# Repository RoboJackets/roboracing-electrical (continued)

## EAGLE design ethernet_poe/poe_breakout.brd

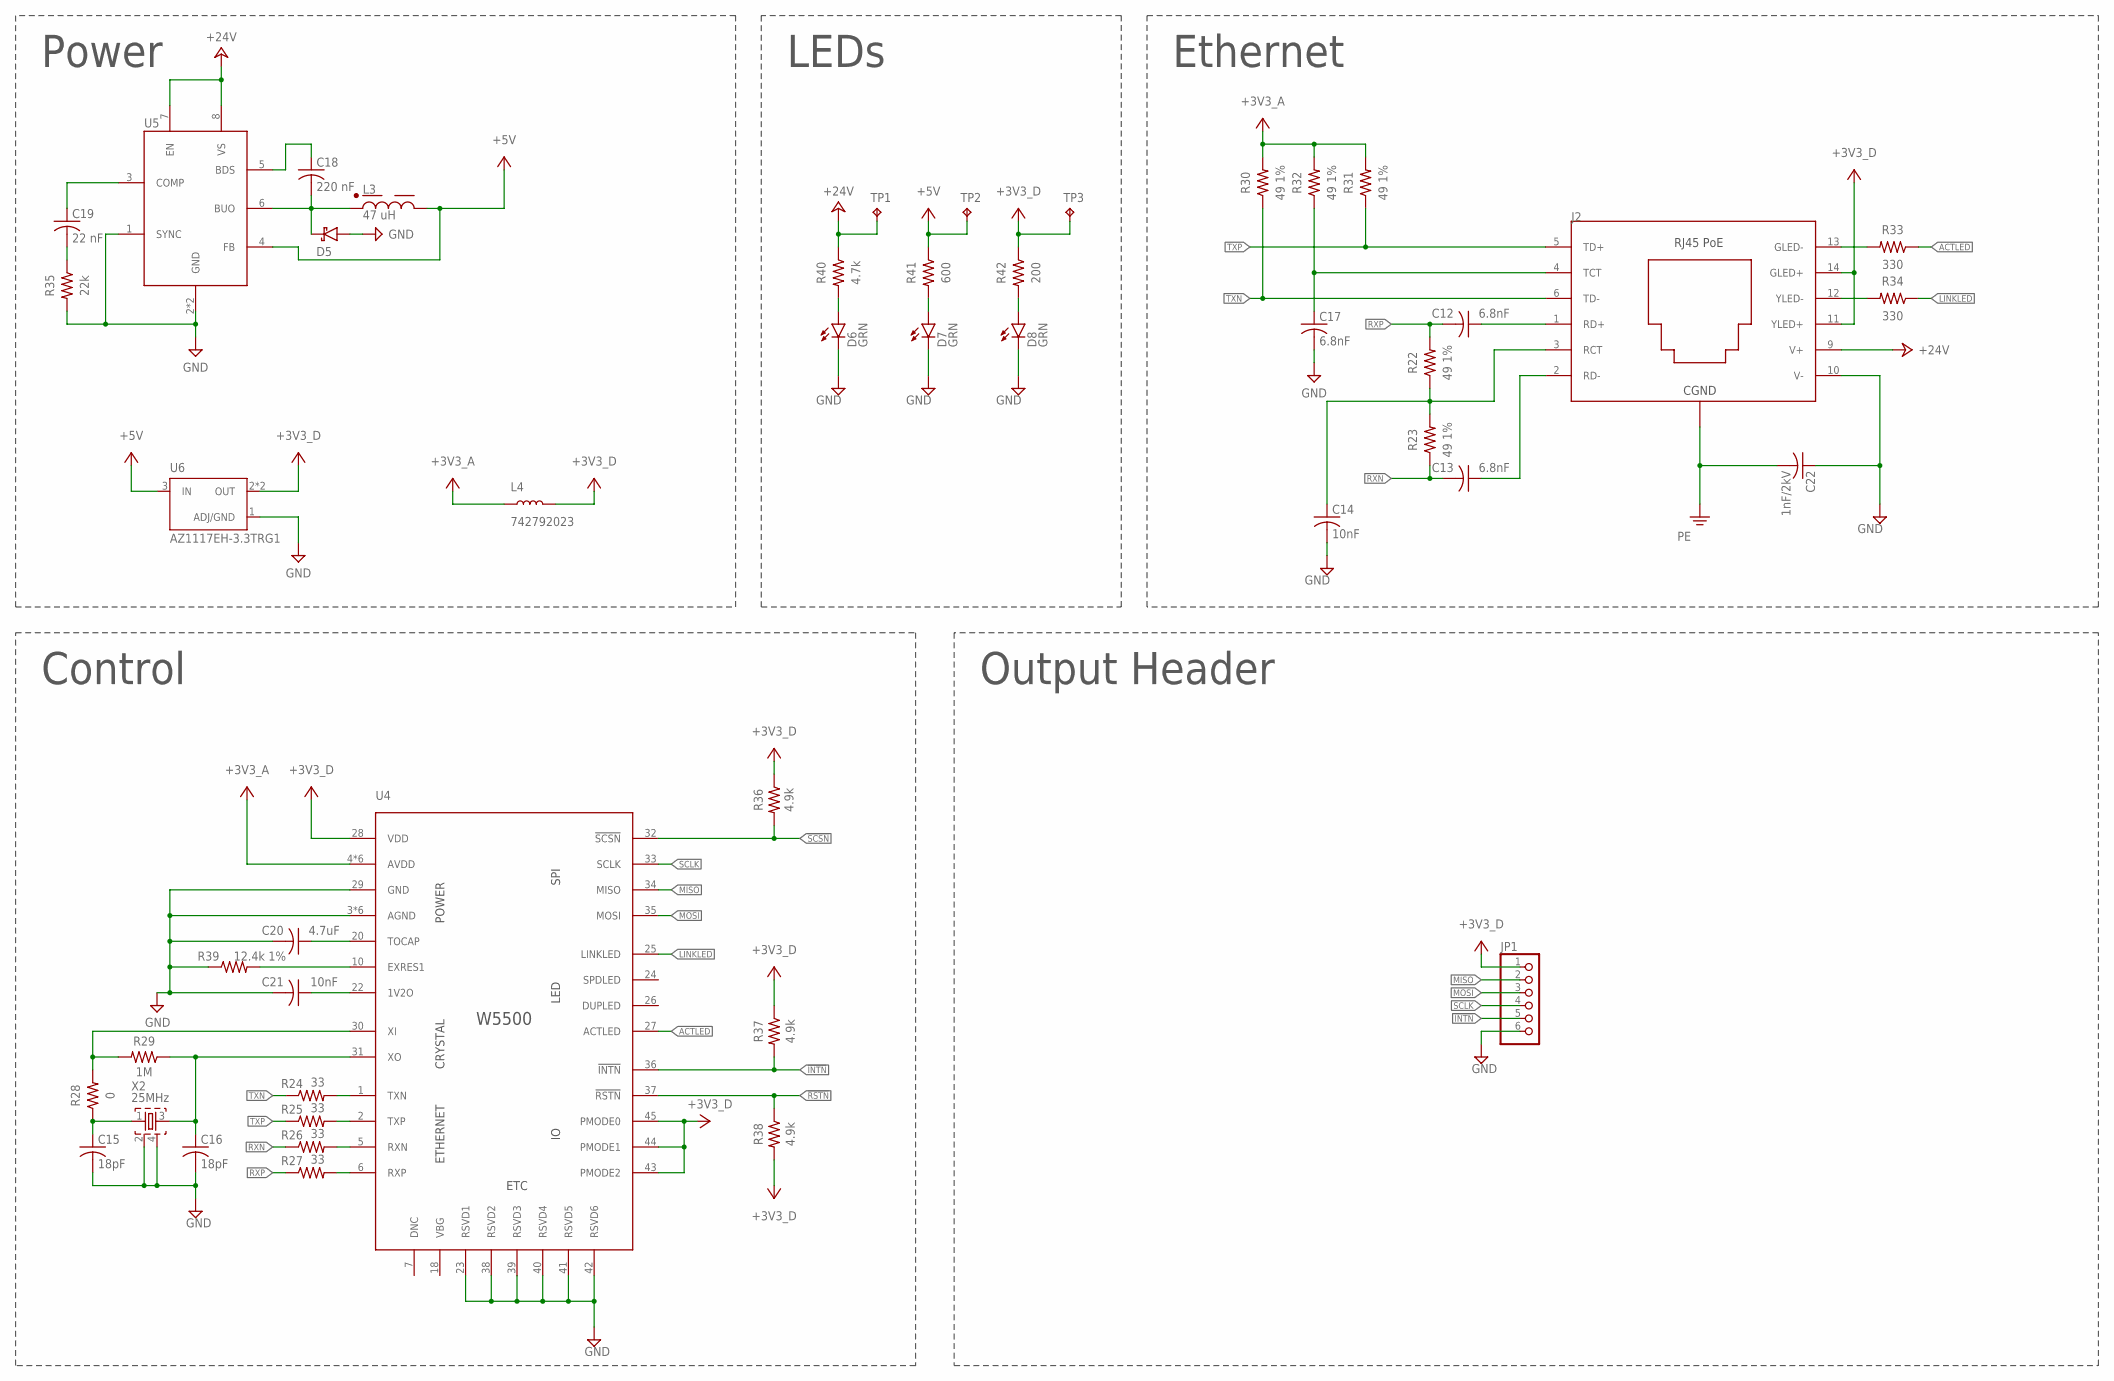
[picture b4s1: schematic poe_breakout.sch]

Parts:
C12, C13, C17: 6.8nF; C0603
C14, C21: 10nF; C0603
C15, C16: 18pF; C0603
C18: 220 nF; C0603
C19: 22 nF; C0603
C20: 4.7uF; C0603
C22: 1nF/2kV; C1206
D5: SCHOTTKYSOD-323; SOD-323
D6, D7, D8: GRN; CHIP-LED0603
J2: ARJP11A; ARJP11A-MBSB-A-B-EMU2
JP1: PINHD-1X6; 1X06
L3: 47 uH; 744771147
L4: 742792023; 0805
R22, R23, R30, R31, R32: 49 1%; R0603
R24, R25, R26, R27: 33; R0603
R28: 0; R0603
R29: 1M; R0603
R33, R34: 330; R0603
R35: 22k; R0603
R36, R37, R38: 4.9k; R0603
R39: 12.4k 1%; R0603
R40: 4.7k; R0603
R41: 600; R0603
R42: 200; R0603
TP1, TP2, TP3: TPB1,27; B1,27
U4: W5500; 48-LQFP
U5: IFX91041; SOIC-8-EXPOSED_PAD
U6: AZ1117EH-3.3TRG1; SOT230P700X180-4N
X2: 25MHz; OSCILLATOR-SMD-2.5X2

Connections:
3V3_LED1: D8.A, R42.2
5V_LED1: D7.A, R41.2
24V_LED1: D6.A, R40.2
!INTN: JP1.5, R37.2, U4.36 (!INTN)
!RSTN: R38.1, U4.37 (!RSTN)
!SCSN: R36.2, U4.32 (!SCSN)
+3V3_A: L4.1, R30.2, R31.2, R32.2, U4.4 (AVDD), U4.8 (AVDD), U4.11 (AVDD), U4.15 (AVDD), U4.17 (AVDD), U4.21 (AVDD)
+3V3_D: J2.11 (YLED+), J2.14 (GLED+), JP1.1, L4.2, R36.1, R37.1, R38.2, R42.1, TP3.TP, U4.28 (VDD), U4.43 (PMODE2), U4.44 (PMODE1), U4.45 (PMODE0), U6.2 (OUT), U6.4 (OUT)
+5V: L3.1, R41.1, TP2.TP, U5.4 (FB), U6.3 (IN)
+24V: J2.9 (V+), R40.1, TP1.TP, U5.7 (EN), U5.8 (VS)
ACTLED: R33.1, U4.27 (ACTLED)
GND: C14.2, C15.2, C16.2, C17.2, C20.2, C21.2, C22.1, D5.A, D6.C, D7.C, D8.C, J2.10 (V-), JP1.6, R35.2, R39.1, U4.3 (AGND), U4.9 (AGND), U4.14 (AGND), U4.16 (AGND), U4.19 (AGND), U4.23 (RSVD1), U4.29 (GND), U4.38 (RSVD2), U4.39 (RSVD3), U4.40 (RSVD4), U4.41 (RSVD5), U4.42 (RSVD6), U4.48 (AGND), U5.1 (SYNC), U5.2 (GND), U5.P$9 (GND), U6.1 (ADJ/GND), X2.2 (SHD1), X2.4 (SHD2)
LINKLED: R34.1, U4.25 (LINKLED)
MISO: JP1.2, U4.34 (MISO)
MOSI: JP1.3, U4.35 (MOSI)
unnamed: R24.2, U4.1 (TXN)
unnamed: R25.2, U4.2 (TXP)
unnamed: R26.2, U4.5 (RXN)
unnamed: R27.2, U4.6 (RXP)
unnamed: C15.1, R28.1, X2.1 (IN)
unnamed: R28.2, R29.2, U4.30 (XI)
unnamed: C16.1, R29.1, U4.31 (XO), X2.3 (OUT)
unnamed: J2.12 (YLED-), R34.2
unnamed: J2.13 (GLED-), R33.2
unnamed: C18.2, D5.C, L3.P$2, U5.6 (BUO)
unnamed: C18.1, U5.5 (BDS)
unnamed: C19.2, R35.1
unnamed: C19.1, U5.3 (COMP)
unnamed: C21.1, U4.22 (1V2O)
unnamed: C20.1, U4.20 (TOCAP)
unnamed: R39.2, U4.10 (EXRES1)
PE: C22.2, J2.15 (CGND), J2.16 (CGND)
RCT1: C14.1, J2.3 (RCT), R22.1, R23.2
RD+1: C12.1, J2.1 (RD+)
RD-1: C13.1, J2.2 (RD-)
RXN: C13.2, R23.1, R26.1
RXP: C12.2, R22.2, R27.1
SCLK: JP1.4, U4.33 (SCLK)
TCT1: C17.1, J2.4 (TCT), R32.1
TXN: J2.6 (TD-), R24.1, R30.1
TXP: J2.5 (TD+), R25.1, R31.1

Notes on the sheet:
Power
Control
LEDs
Ethernet
Output Header

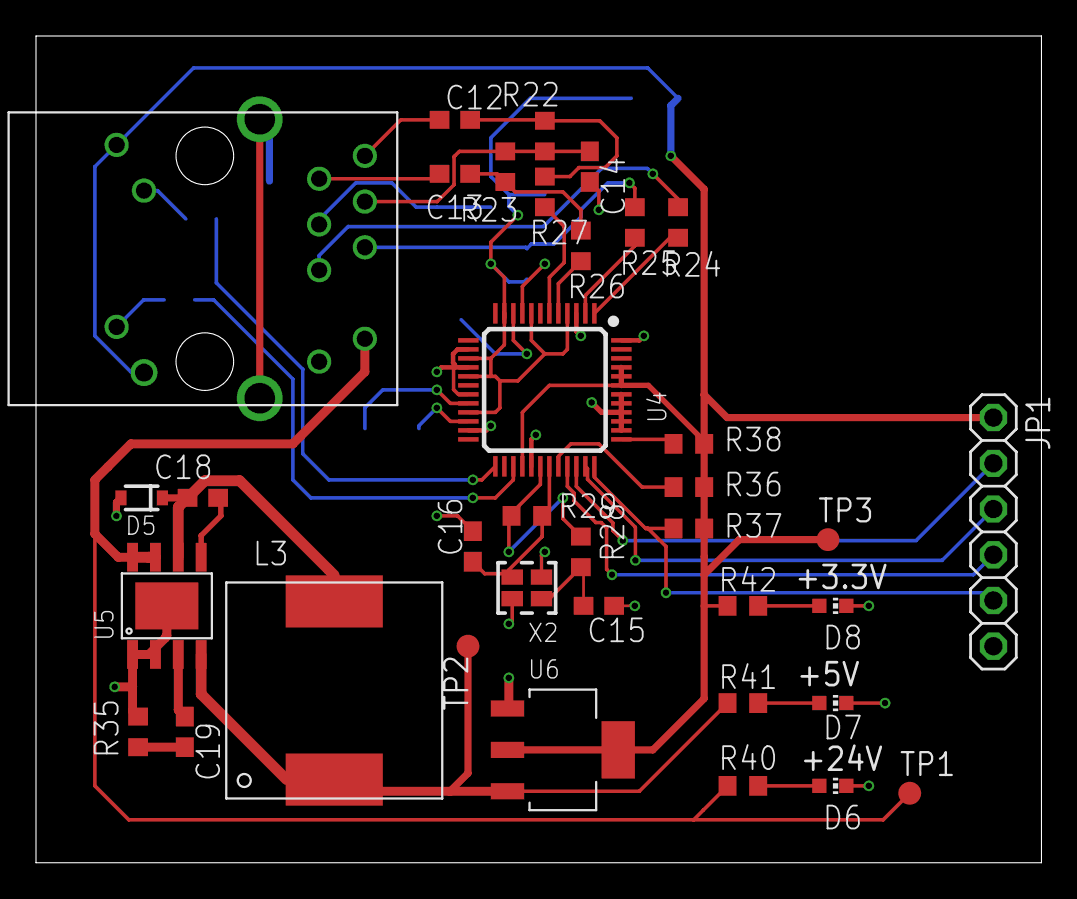
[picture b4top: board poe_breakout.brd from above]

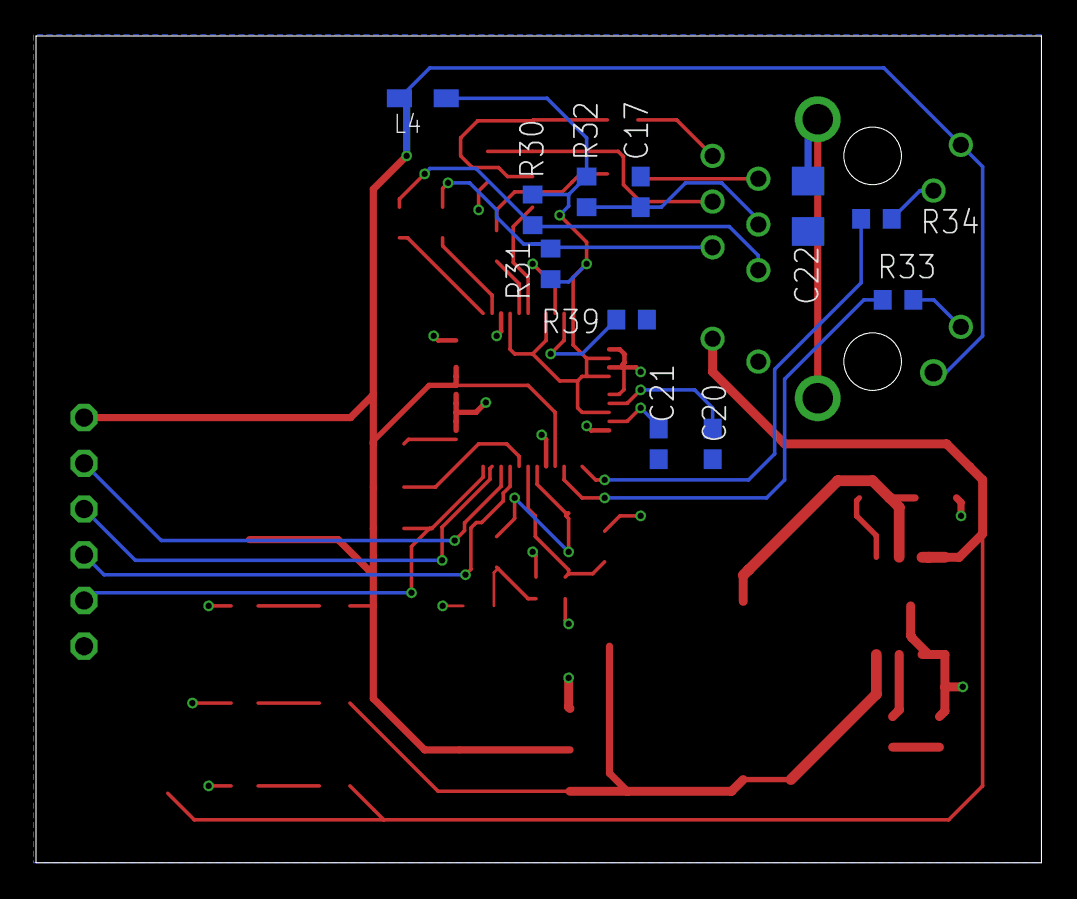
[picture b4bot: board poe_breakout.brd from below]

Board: 2 copper layers, 55.9 x 45.9 mm, 47 parts (11 on the bottom side), 41 nets.

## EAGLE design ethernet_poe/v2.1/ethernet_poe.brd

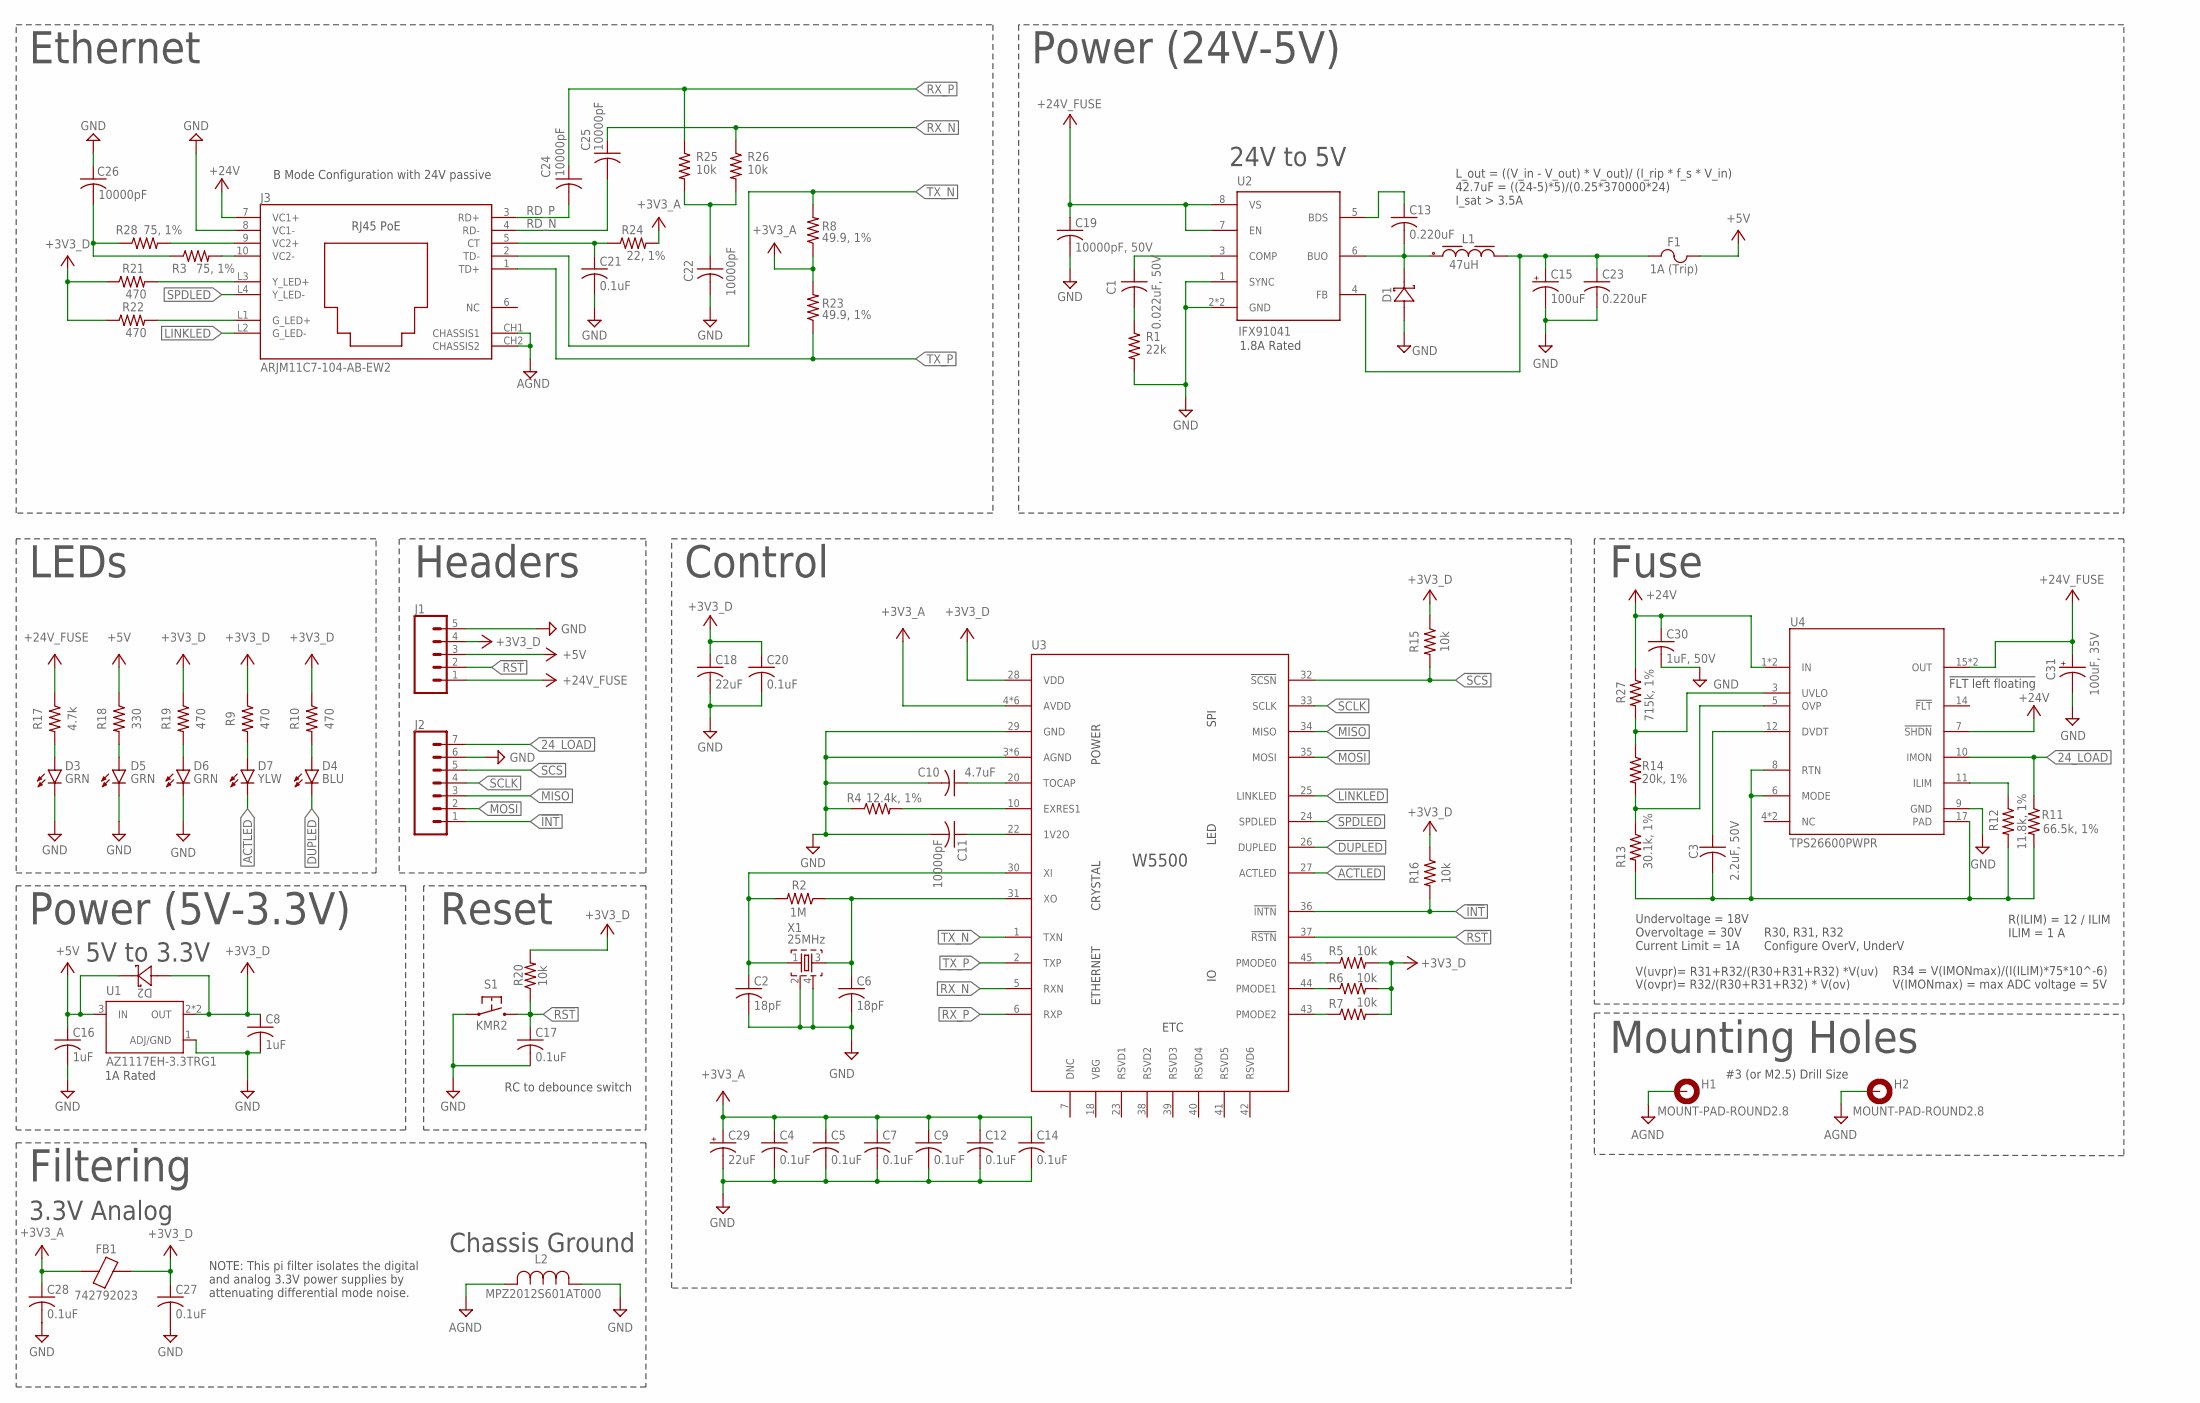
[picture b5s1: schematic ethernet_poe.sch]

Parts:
C1: 0.022uF, 50V; C0603
C2, C6: 18pF; C0603
C3: 2.2uF, 50V; C0603
C4, C5, C7, C9, C12, C14, C17, C20, C21: 0.1uF; C0402
C8, C16: 1uF; C0603
C10: 4.7uF; C0603
C11, C24, C25: 10000pF; C0402
C13, C23: 0.220uF; C0603
C15: 100uF; E2-5
C18: 22uF; C0603
C19: 10000pF, 50V; C0603
C22, C26: 10000pF; C0603
C27, C28: 0.1uF; C0603
C29: 22uF; PANASONIC_C
C30: 1uF, 50V; C0603
C31: 100uF, 35V; E2,5-7
D1, D2: NTS260ESFT3G; SOD123FL_DIO
D3, D5, D6: GRN; CHIP-LED0603
D4: BLU; CHIP-LED0603
D7: YLW; CHIP-LED0603
F1: 1A (Trip); 0ZCG_BEL
FB1: 742792023; 0805
H1, H2: MOUNT-PAD-ROUND2.8; 2,8-PAD
J1: CONN_05; 1X05
J2: CONN_07; 1X07
J3: ARJM11C7-104-AB-EW2; CONN_EW_ABR
L1: 47uH; WE-PD_1210
L2: MPZ2012S601AT000; IND_2012_TDK
R1: 22k; R0603
R2: 1M; R0402
R3, R28: 75, 1%; R0603
R4: 12.4k, 1%; R0603
R5, R6, R7, R15, R16, R20, R25, R26: 10k; R0603
R8, R23: 49.9, 1%; R0402
R9, R10, R19, R21, R22: 470; R0603
R11: 66.5k, 1%; R0603
R12: 11.8k, 1%; R0603
R13: 30.1k, 1%; R0603
R14: 20k, 1%; R0603
R17: 4.7k; R0603
R18: 330; R0603
R24: 22, 1%; R0603
R27: 715k, 1%; R0603
S1: KMR2
U1: AZ1117EH-3.3TRG1; SOT230P700X180-4N
U2: IFX91041; SOIC-8-EXPOSED_PAD
U3: W5500; 48-LQFP
U4: TPS26600PWPR; PWP0016H_N
X1: 25MHz; OSCILLATOR-SMD-2.5X2

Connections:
3V3_LED: D6.A, R19.2
3V3_LED1: D7.A, R9.2
3V3_LED2: D4.A, R10.2
5V_LED: D5.A, R18.2
5V_RAW: C13.2, D1.1, L1.1, U2.6 (BUO)
24V_LED: D3.A, R17.2
24_LOAD: J2.7, R11.1, U4.10 (IMON)
!INT: J2.1, R16.2, U3.36 (!INTN)
!RST: C17.1, J1.2, R20.1, S1.2.1 (2), S1.2.2 (2), U3.37 (!RSTN)
!SCS: J2.5, R15.2, U3.32 (!SCSN)
+3V3_A: C4.1, C5.1, C7.1, C9.1, C12.1, C14.1, C28.1, C29.+, FB1.1, R8.1, R23.2, R24.2, U3.4 (AVDD), U3.8 (AVDD), U3.11 (AVDD), U3.15 (AVDD), U3.17 (AVDD), U3.21 (AVDD)
+3V3_D: C8.1, C18.1, C20.1, C27.1, D2.2, FB1.2, J1.4, R5.2, R6.2, R7.2, R9.1, R10.1, R15.1, R16.1, R19.1, R20.2, R21.1, R22.1, U1.2 (OUT), U1.4 (OUT), U3.28 (VDD)
+5V: C16.1, D2.1, F1.2, J1.3, R18.1, U1.3 (IN)
+5V_PREFUSE: C15.+, C23.1, F1.1, L1.2, U2.4 (FB)
+24V: C30.1, J3.7 (VC1+), R27.1, U4.1 (IN), U4.2 (IN), U4.7 (!SHDN)
+24V_FUSE: C19.1, C31.+, J1.1, R17.1, U2.7 (EN), U2.8 (VS), U4.15 (OUT), U4.16 (OUT)
ACTLED: D7.C, U3.27 (ACTLED)
AGND: H1.B2,8, H2.B2,8, J3.CH1 (CHASSIS1), J3.CH2 (CHASSIS2), L2.2
CT: C21.1, J3.5 (CT), R24.1
DUPLED: D4.C, U3.26 (DUPLED)
GND: C2.2, C4.2, C5.2, C6.2, C7.2, C8.2, C9.2, C10.2, C11.2, C12.2, C14.2, C15.-, C16.2, C17.2, C18.2, C19.2, C20.2, C21.2, C22.2, C23.2, C26.1, C27.2, C28.2, C29.-, C30.2, C31.-, D1.2, D3.C, D5.C, D6.C, J1.5, J2.6, J3.8 (VC1-), L2.1, R1.2, R4.1, S1.1.1 (1), S1.1.2 (1), U1.1 (ADJ/GND), U2.1 (SYNC), U2.2 (GND), U2.9 (GND), U3.3 (AGND), U3.9 (AGND), U3.14 (AGND), U3.16 (AGND), U3.19 (AGND), U3.29 (GND), U3.48 (AGND), U4.9 (GND), X1.2 (SHD1), X1.4 (SHD2)
G_LED+: J3.L1 (G_LED+), R22.2
LINKLED: J3.L2 (G_LED-), U3.25 (LINKLED)
MISO: J2.3, U3.34 (MISO)
MOSI: J2.2, U3.35 (MOSI)
unnamed: R5.1, U3.45 (PMODE0)
unnamed: R6.1, U3.44 (PMODE1)
unnamed: R7.1, U3.43 (PMODE2)
unnamed: J3.9 (VC2+), R28.2
unnamed: R14.1, R27.2, U4.3 (UVLO)
unnamed: J3.10 (VC2-), R3.2
unnamed: C6.1, R2.1, U3.31 (XO), X1.3 (OUT)
unnamed: C26.2, R3.1, R28.1
unnamed: C2.1, R2.2, U3.30 (XI), X1.1 (IN)
unnamed: C13.1, U2.5 (BDS)
unnamed: C1.2, R1.1
unnamed: C1.1, U2.3 (COMP)
unnamed: C11.1, U3.22 (1V2O)
unnamed: C10.1, U3.20 (TOCAP)
unnamed: R4.2, U3.10 (EXRES1)
unnamed: R13.1, R14.2, U4.5 (OVP)
unnamed: C3.1, U4.12 (DVDT)
unnamed: R12.1, U4.11 (ILIM)
RD_N: C25.2, J3.4 (RD-)
RD_P: C24.2, J3.3 (RD+)
RTN: C3.2, R11.2, R12.2, R13.2, U4.6 (MODE), U4.8 (RTN), U4.17 (PAD)
RX_FILTER: C22.1, R25.2, R26.2
RX_N: C25.1, R26.1, U3.5 (RXN)
RX_P: C24.1, R25.1, U3.6 (RXP)
SCLK: J2.4, U3.33 (SCLK)
SPDLED: J3.L4 (Y_LED-), U3.24 (SPDLED)
TX_N: J3.2 (TD-), R8.2, U3.1 (TXN)
TX_P: J3.1 (TD+), R23.1, U3.2 (TXP)
Y_LED+: J3.L3 (Y_LED+), R21.2

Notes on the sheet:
Power (24V-5V)
Control
LEDs
Ethernet
Headers
RC to debounce switch
Reset
24V to 5V
5V to 3.3V
3.3V Analog
B Mode Configuration with 24V passive
NOTE: This pi filter isolates the digital and analog 3.3V power supplies by attenuating differential mode noise.
R(ILIM) = 12 / ILIM ILIM = 1 A
Undervoltage = 18V Overvoltage = 30V Current Limit = 1A
R30, R31, R32 Configure OverV, UnderV
V(ovpr)= R32/(R30+R31+R32) * V(ov)
V(uvpr)= R31+R32/(R30+R31+R32) *V(uv)
Fuse
!FLT left floating
Mounting Holes
Power (5V-3.3V)
Filtering
Chassis Ground
R34 = V(IMONmax)/(I(ILIM)*75*10^-6) V(IMONmax) = max ADC voltage = 5V
1.8A Rated
#3 (or M2.5) Drill Size
1A Rated
L_out = ((V_in - V_out) * V_out)/ (I_rip * f_s * V_in) 42.7uF = ((24-5)*5)/(0.25*370000*24) I_sat > 3.5A

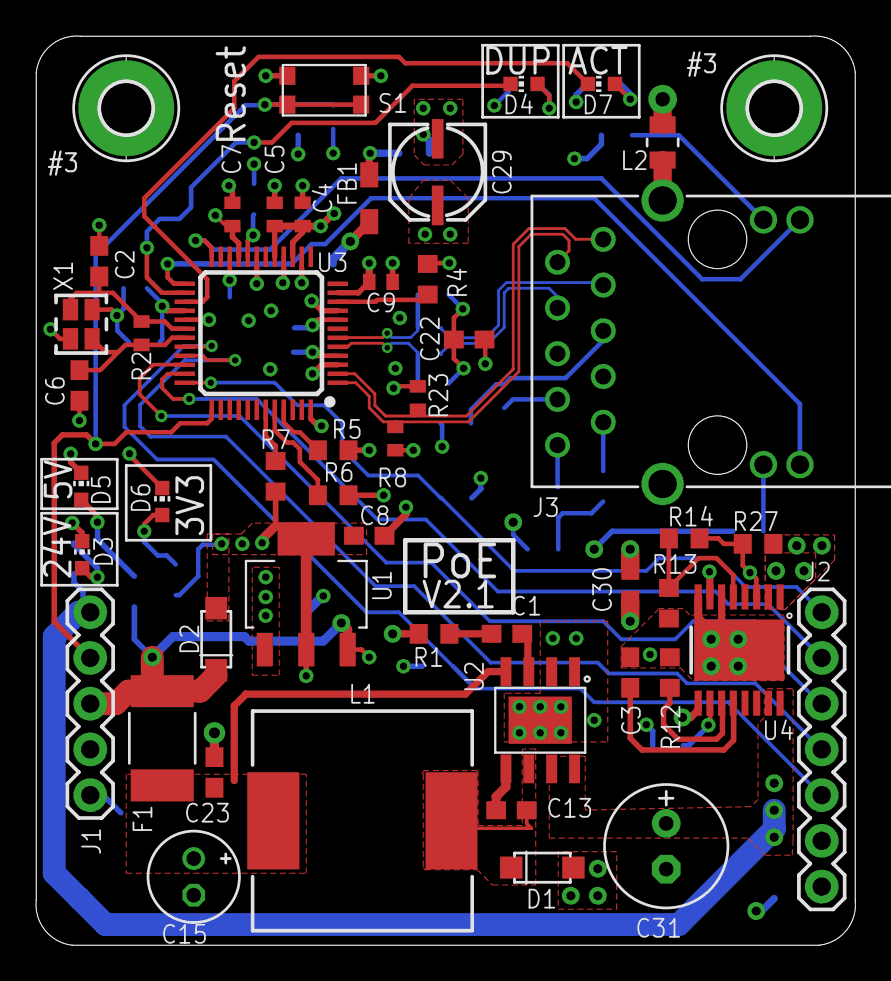
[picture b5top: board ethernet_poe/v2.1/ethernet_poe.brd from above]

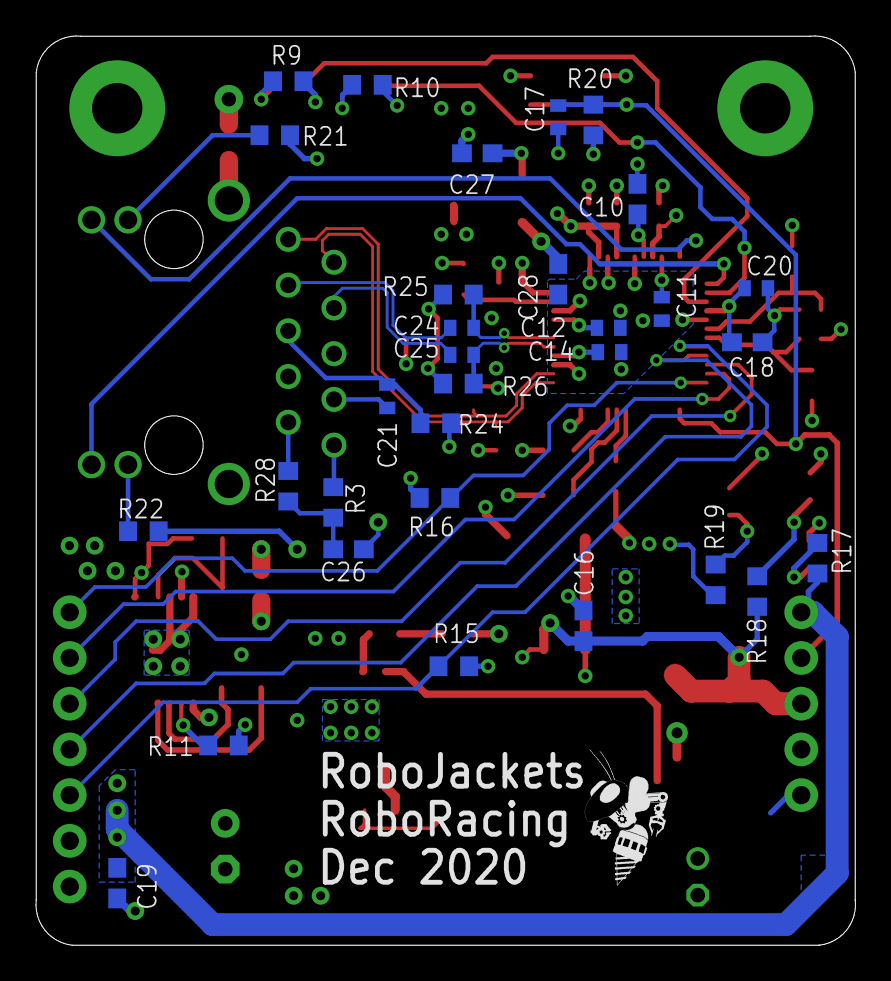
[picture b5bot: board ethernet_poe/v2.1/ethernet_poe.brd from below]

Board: 4 copper layers, 45.5 x 50.5 mm, 82 parts (32 on the bottom side), 54 nets.

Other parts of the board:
U$2: ROBOBUZZ_0.4X
